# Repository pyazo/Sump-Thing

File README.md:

# Sump Thing

#### An open sourced approach to aquarium management using the Arduino ESP8266 module
---

## Features

- Open source from front to back
- 4 smart outlets
- 2 thermocouple sensors
- 2 water level sensors
- Built in event tracking
- Full control via wifi from anywhere in the world
- Historical data and analytics tracking

## Why?

The goal is to build something scalable and easy to build so everyone can have sump thing running under their tank.

### Where do I get the hardware?

At this time we are not selling our boards. While we flesh out the software and get out protoype working even better we will continue
planning on building a circuitboard with the esp8266 module built in.

We will update this section as the boards become available.

##  Contributions

At this time we are not accepting contributions outside of our core team, in the future we will open this up.

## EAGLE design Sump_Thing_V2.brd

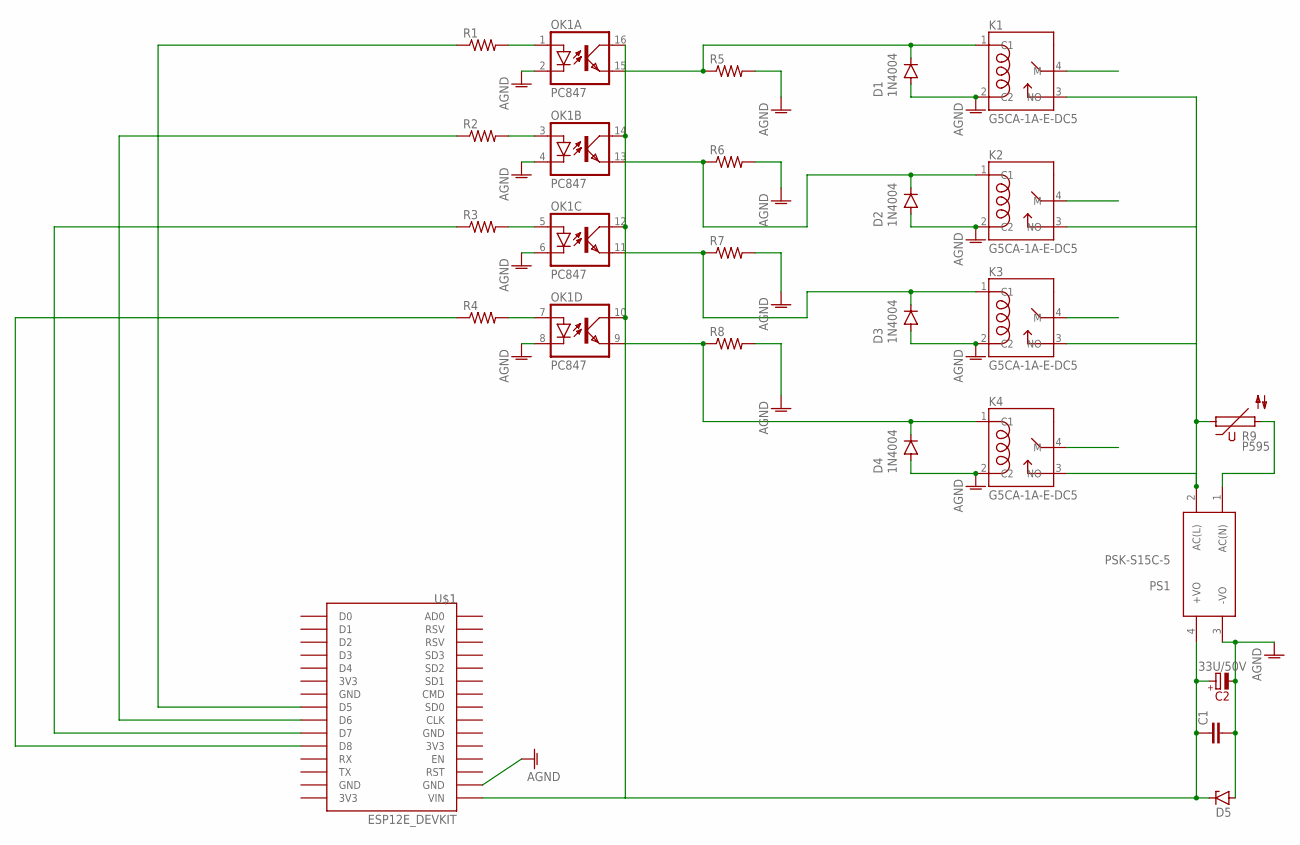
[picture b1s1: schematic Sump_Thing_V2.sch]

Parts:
C1: C2.5/2; C2.5-2
C2: 33U/50V; E3,5-8
D1, D2, D3, D4: 1N4004; DO41-10
D5: ZENER-DIODESMB; SMB
K1, K2, K3, K4: G5CA-1A-E-DC5; RELAY_G5CA-1A-E-DC5
OK1: PC847; DIL16
PS1: PSK-S15C-5; CONV_PSK-S15C-5
R1, R2, R3, R4, R5, R6, R7, R8: R-US_0207/10; 0207/10
R9: P595
U$1: ESP12E_DEVKIT

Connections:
AGND: C1.2, C2.-, D1.A, D2.A, D3.A, D4.A, D5.A, K1.2 (C2), K2.2 (C2), K3.2 (C2), K4.2 (C2), OK1.2 (C), OK1.4 (C), OK1.6 (C), OK1.8 (C), PS1.3 (-VO), R5.2, R6.2, R7.2, R8.2, U$1.GND@1 (GND)
unnamed: K1.3 (NO), K2.3 (NO), K3.3 (NO), K4.3 (NO), PS1.2 (AC(L)), R9.1
unnamed: D2.C, K2.1 (C1), OK1.13 (EMIT), R6.1
unnamed: D3.C, K3.1 (C1), OK1.11 (EMIT), R7.1
unnamed: D4.C, K4.1 (C1), OK1.9 (EMIT), R8.1
unnamed: D1.C, K1.1 (C1), OK1.15 (EMIT), R5.1
unnamed: C1.1, C2.+, D5.C, OK1.10 (COL), OK1.12 (COL), OK1.14 (COL), OK1.16 (COL), PS1.4 (+VO), U$1.VIN
unnamed: OK1.3 (A), R2.2
unnamed: OK1.1 (A), R1.2
unnamed: OK1.5 (A), R3.2
unnamed: OK1.7 (A), R4.2
unnamed: R1.1, U$1.D5
unnamed: R2.1, U$1.D6
unnamed: R3.1, U$1.D7
unnamed: R4.1, U$1.D8
unnamed: PS1.1 (AC(N)), R9.2

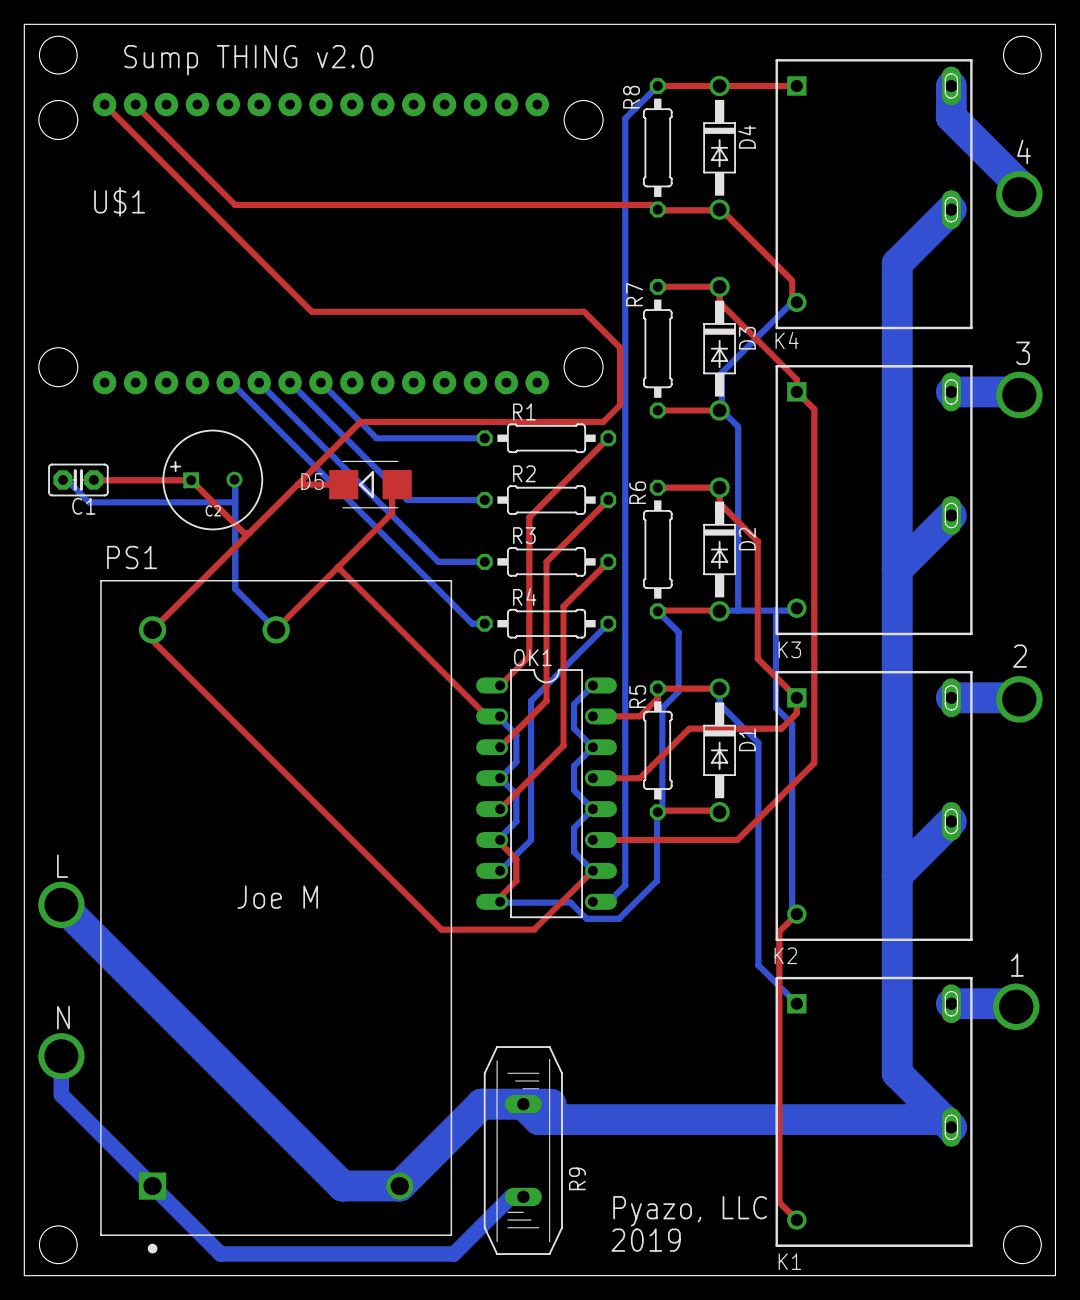
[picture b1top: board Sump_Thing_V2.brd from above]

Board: 2 copper layers, 84.8 x 102.9 mm, 23 parts (0 on the bottom side), 16 nets.

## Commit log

2018-07-15 Initial
2018-10-06 Fixed data types
2018-10-06 No more stack overflow :D
2018-10-06 Update pin numbers, fix some logic
2018-10-06 Cleaned up code
2018-10-07 Refactored some code
2018-10-08 WIP: extract some code
2018-10-08 Working code!
2018-10-08 Remove debug
2018-10-08 Clean up code some
2018-10-08 Create LICENSE
2018-10-09 Updates on command handling, add command for single outlet toggle
2018-10-10 Updated some func names
2019-11-02 Remove brd + sch files
2019-11-05 Basic wifi broadcast with DNS forwarding
2019-11-11 Read from SPIFFS file system
2019-11-14 Real JSON return from /networks
2020-04-09 Got wifi working
2020-04-14 Save WiFi and connect to saved WiFi on reboot
